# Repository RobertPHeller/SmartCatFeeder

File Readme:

# Smart Cat Feeder

A smart cat feeder, an "upgrade" from the feeder on Thingiverse.com, using an 
ESP32-S2 Dev board -- a more powerful processor.  It will have a touch screen,
and provide a web server over WiFi.  It will use a load cell to measure how 
full the food bowl is, it will have a sensor to check when the food bin is low
and have a battery backup to operate in the event of a power failure, to 
insure your cat will be feed when the power goes out.

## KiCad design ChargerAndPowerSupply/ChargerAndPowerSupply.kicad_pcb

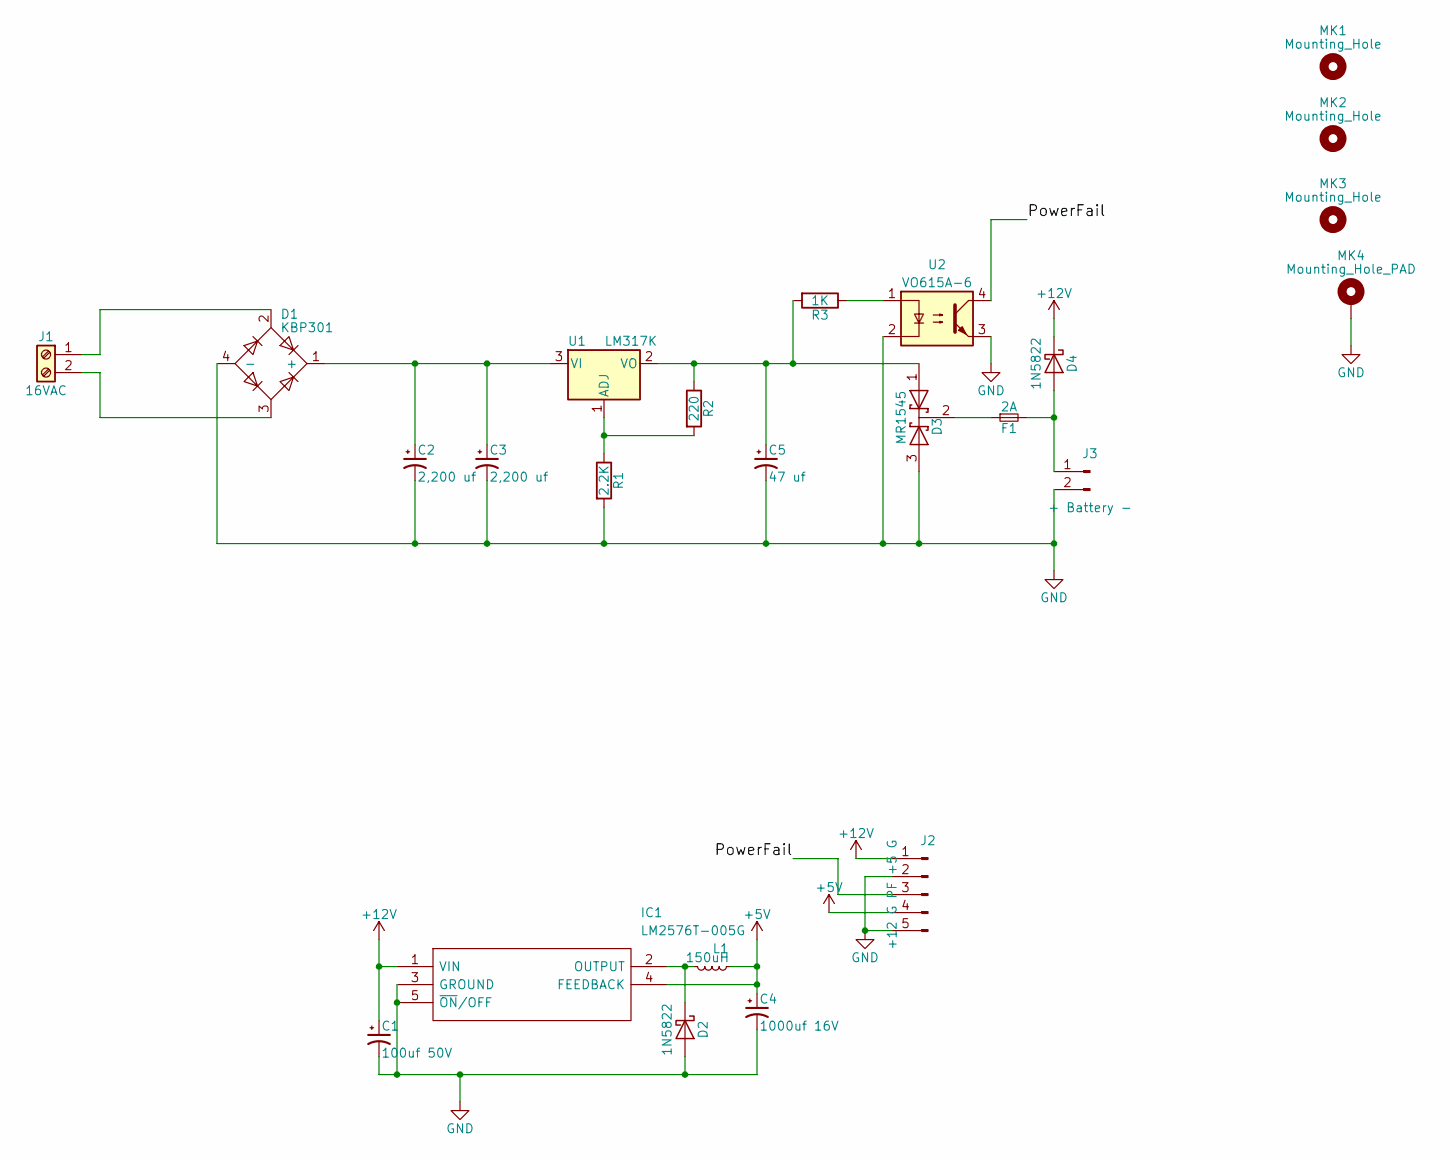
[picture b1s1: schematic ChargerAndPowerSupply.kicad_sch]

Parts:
C1: 100uf 50V; CP_Radial_D8.0mm_P5.00mm; Mouser Part Number 667-EEU-FR1H101B
C2, C3: 2,200 uf; CP_Radial_D16.0mm_P7.50mm; Mouser Part Number 140-REA222M1HBK1636P
C4: 1000uf 16V; CP_Radial_D10.0mm_P5.00mm; Mouser Part Number 667-EEU-FR1C102
C5: 47 uf; CP_Radial_D6.3mm_P2.50mm; Mouser Part Number 140-REA470M1HBK0611P
D1: KBP301; KBP301G; Mouser Part Number 905-KBP301
D2, D4: 1N5822; D_DO-201AD_P15.24mm_Horizontal
D3: MR1545; TO-220_Vertical
F1: 2A; MRT2; Mouser Part Number 530-MRT2
IC1: LM2576T-005G; TO-220-5_Pentawatt_Multiwatt-5_Vertical_StaggeredType1; Mouser2 Part Number 863-LM2576T-005G
J1: 16VAC; TerminalBlock_Pheonix_MKDS1.5-2pol; Mouser Part Numer 651-1017491
J2: +12 G PF +5 G; 26607050
J3: + Battery -; 26607020
L1: 150uH; L_Toroid_Vertical_L24.6mm_W15.5mm_P11.44mm_Pulse_KM-4; Mouser Part Number 673-PE-53113NL
MK1, MK2, MK3: Mounting_Hole; MountingHole_4.5mm
MK4: Mounting_Hole_PAD; MountingHole_4.5mm_Pad
R1: 2.2K; R_Axial_DIN0204_L3.6mm_D1.6mm_P7.62mm_Horizontal; Mouser Part Number 603-CFR-12JT-52-2K2
R2: 220; R_Axial_DIN0204_L3.6mm_D1.6mm_P7.62mm_Horizontal; Mouser Part Number 603-CFR-12JT-52-220R
R3: 1K; R_Axial_DIN0204_L3.6mm_D1.6mm_P7.62mm_Horizontal; Mouser Part Number 603-CFR-12JB-52-1K
U1: LM317K; TO-220_Vertical; Mouser Part Number LM317KCT
U2: VO615A-6; DIP-4_W7.62mm

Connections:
+5V: C4.1, IC1.4 (FEEDBACK), J2.4, L1.1
+12V: C1.1, D4.1 (K), IC1.1 (VIN), J2.1
/PowerFail: J2.3, U2.4
GND: C1.2, C2.2, C3.2, C4.2, C5.2, D1.4 (-), D2.2 (A), D3.3 (A), IC1.3 (GROUND), IC1.5 (~ON/OFF), J2.2, J2.5, J3.2, MK4.1, R1.2, U2.2, U2.3
unnamed: C2.1, C3.1, D1.1 (+), U1.3 (VI)
unnamed: C5.1, D3.1 (A), R2.1, R3.2, U1.2 (VO)
unnamed: D1.2, J1.1
unnamed: D1.3, J1.2
unnamed: D2.1 (K), IC1.2 (OUTPUT), L1.2
unnamed: D3.2 (K), F1.1
unnamed: D4.2 (A), F1.2, J3.1
unnamed: R1.1, R2.2, U1.1 (ADJ)
unnamed: R3.1, U2.1

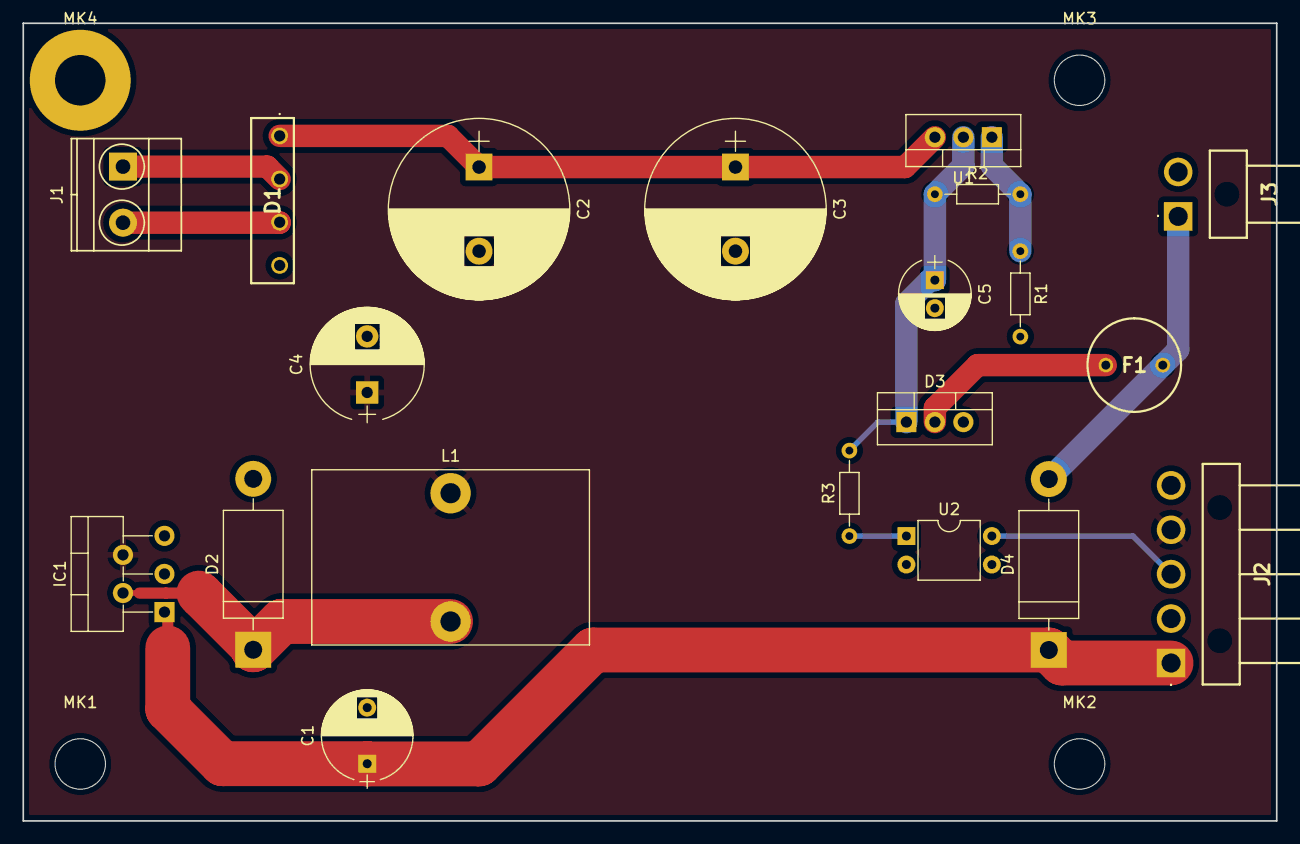
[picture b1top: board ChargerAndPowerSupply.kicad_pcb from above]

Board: 2 copper layers, 111.8 x 71.1 mm, 24 parts (0 on the bottom side), 13 nets.

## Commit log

2021-09-12 Add initial files
2021-09-13 Food Bin mostly done.
2021-09-13 Completing the feed bin, added holes for auger mount.
2021-09-14 Completed Laser Diode drive circuit.
2021-09-15 Removed LaserFeedBinEmptyCheck Circuits.
2021-09-15 Add Waveshare Laser Sensor information.
2021-09-17 Add Pi4 board.
2021-09-17 Add Server Connections.
2021-09-18 Charger and Power Supply board completed.
2021-09-18 Minor update -- footprints and 3D shapes.
2021-09-20 Added additional dimensions.
2021-09-20 Added PS box and board 3D Models.
2021-09-21 Completed PS Box.
2021-09-21 Added PS Box to food bin.
2021-09-23 Complete Food Bin 3D model.
2024-08-11 Upgrade KiCAD files.
2024-08-12 Add touch display.
2024-08-13 Added additional breakout boards: rtc, load cell, power fail gpio.
2024-08-13 Add screen mounting bracket.
2024-08-13 BatteryBox completion: fingers for back, beams for top.
2024-08-13 Remove extra space for RPi touch screen, properly position beams for battery top.
2024-08-14 Add adafruitTFT.
2024-08-15 Add wire hole.
2024-08-15 Update Readme.
2024-08-15 Remove RPi, replace with ESP32-S3 Feather.
2024-08-15 Start on the firmware.
2024-08-15 Add Revision handling, create start screen, error message handling.
2024-08-15 Fix Makefile (revision opts).
2024-08-16 Updates to Readme (add links), move wire hole to accommodate a USB-C power cable, remove protoboard for power.
2024-08-16 Updates to Readme.
2024-08-17 Working on the firmware.
2024-08-18 Add additional I2C boards.
2024-08-18 Add Clock and Force Sensor boaards.
2024-08-18 Add gear motor with mount plates.
2024-08-19 Gear Motor Mount for auger.
2024-08-19 Add agitator, with motor.
2024-08-20 Add vl6180x.
2024-08-21 Battery box updates.
2024-08-22 Add strain guage and bowl, Adjust things to fit bowl.
2024-08-22 Add bowl support box.
2024-08-22 Add bowl support box screw holes.
2024-08-22 Add Power cord notches and back mounting beams.
2024-08-22 Finalize things, make first draft of panel cut sheets.
2024-08-23 Finalized.
2024-08-23 Update readme: parts and materials list.
2024-08-23 Add sleep so TechDrawGui.exportPageAsSvg will work.
2024-08-23 Remove WaveshareLaserSensor.
2024-08-24 Working on firmware.
2024-08-24 Add Clock Display class.
2024-08-25 Complete draft of virtual keyboard.
2024-08-26 Cleanup Keyboard code.
2024-08-26 Working on prefs screens.
2024-08-27 Start refactering code.
2024-08-27 Completed refactering code, moving forward.
2024-08-28 Preferences are complete.
2024-08-28 Completed spinbox.
2024-08-29 Completer AMPMSelectbox.
2024-08-29 Completed Schedule.
2024-08-29 Completed Sensor code. (Need calibration!)
2024-08-29 Completed Mechanical.
2024-08-30 Completed settings page.
2024-08-30 Fix mounting hole problem with motor mount.
2024-08-31 Start on schedule management and manual feed webpages. Sort schedule vector.
2024-08-31 Simplify EarlierSched. Complete ScheduleManagementPage.
2024-09-01 Completed and waiting for testing with actual hardware.
2024-09-01 Charger & PS bit drill and cut sheet. Readme updates.
2024-09-02 Finalize charger and ps.
2024-09-02 Tweaks to the Charger PS.
2024-09-29 Update Makefile: use build.path pref.
2024-09-29 Small fix to Mechanical.cpp.
2024-11-03 Add Screen flap.
2024-11-03 Build for a 4meg Feather.
2024-11-10 nothing
2024-11-10 Revert "Build for a 4meg Feather."
    This reverts commit 0be278e8015b755209baf81524f555d6c02cfab5.
2024-11-10 Revert "nothing"
    This reverts commit 02002390b936040632b82b980f4eb395d3158ec8.
2024-11-10 Provide targets for both 8Meg and 4Meg feathers.
2024-11-26 Update auger mount holes and add auger mount.
2024-12-02 Add Wood BOM.
2024-12-05 Adjust battery box size.
2025-03-28 Start V2 bin design update.
2025-03-29 Continue V2 bin design update.
2025-03-30 Add realistic Adafruit NAU7802.
2025-03-31 Final positioning Adafruit NAU7802. Enlarge wire hole.
2025-04-01 Add auger motor mount and motor.
2025-04-06 Redo panel cut sheets.
2025-04-15 Add nau7802_test -- needed for scale calibration.
